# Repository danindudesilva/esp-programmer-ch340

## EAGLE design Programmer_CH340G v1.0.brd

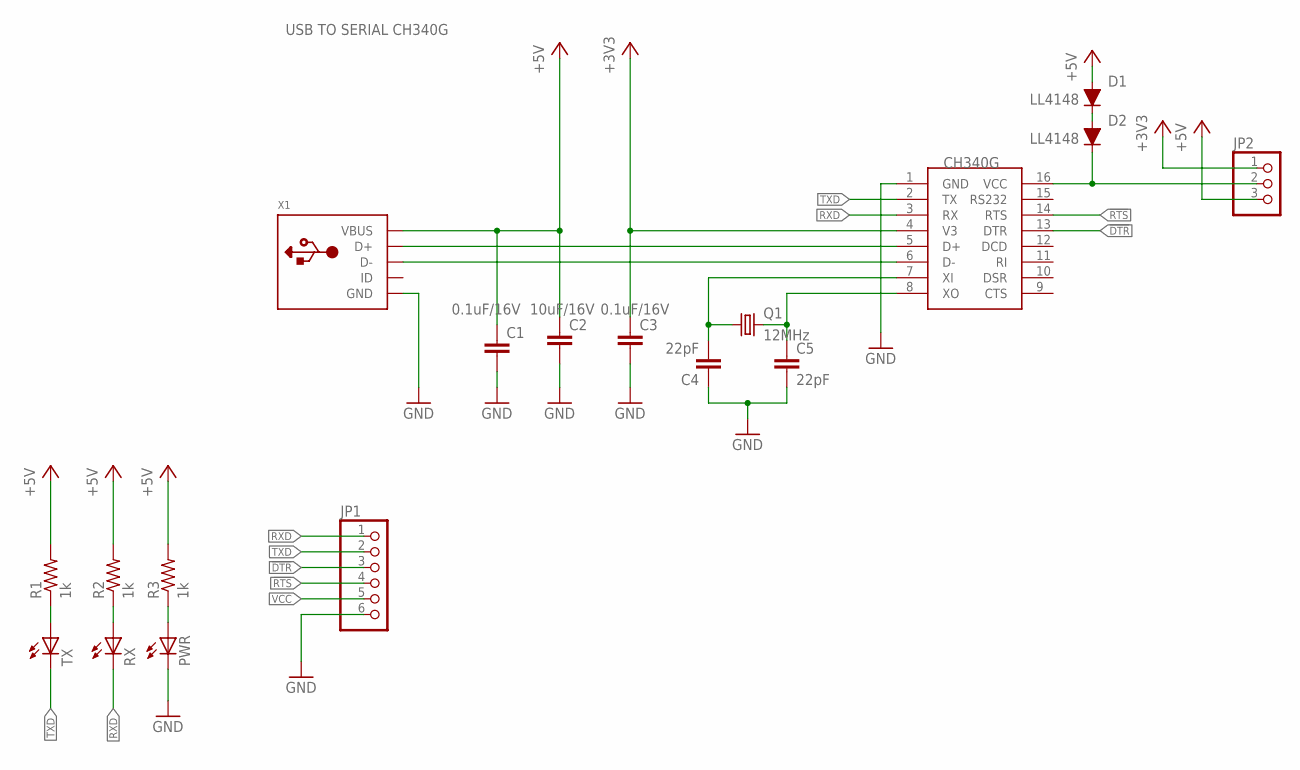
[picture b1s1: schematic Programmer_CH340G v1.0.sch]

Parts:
C1, C3: 0.1uF/16V; C0805K
C2: 10uF/16V; C0805K
C4, C5: 22pF; C0805K
D1, D2: LL4148; SOD80
JP1: PINHD-1X6; 1X06
JP2: PINHD-1X3; 1X03
PWR: LEDCHIP-LED0805; CHIP-LED0805
Q1: 12MHz; HC49U-V
R1, R2, R3: 1k; M0805
RX: LEDCHIP-LED0805; CHIP-LED0805
TX: LEDCHIP-LED0805; CHIP-LED0805
U1: CH340G; SOIC16
X1: USB_MICRO_20329_V2; 4UCONN_20329_V2

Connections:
!DTR: JP1.3, U1.13 (DTR)
!RTS: JP1.4, U1.14 (RTS)
+3V3: C3.1, JP2.1, U1.4 (V3)
+5V: C1.1, C2.1, D1.2 (A), JP2.3, R3.2, X1.VBUS
GND: C1.2, C2.2, C3.2, C4.1, C5.2, JP1.6, PWR.C, U1.1 (GND), X1.BASE@1 (GND), X1.BASE@2 (GND), X1.GND, X1.SPRT@1 (GND), X1.SPRT@2 (GND), X1.SPRT@3 (GND), X1.SPRT@4 (GND)
unnamed: PWR.A, R3.1
unnamed: C4.2, Q1.1, U1.7 (XI)
unnamed: D1.1 (C), D2.2 (A)
unnamed: C5.1, Q1.2, U1.8 (XO)
unnamed: U1.5 (D+), X1.D+
unnamed: U1.6 (D-), X1.D-
unnamed: R1.1, TX.A
unnamed: R2.1, RX.A
RXD: JP1.1, RX.C, U1.3 (RX)
TXD: JP1.2, TX.C, U1.2 (TX)
VCC: D2.1 (C), JP1.5, JP2.2, R1.2, R2.2, U1.16 (VCC)

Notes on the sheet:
USB TO SERIAL CH340G

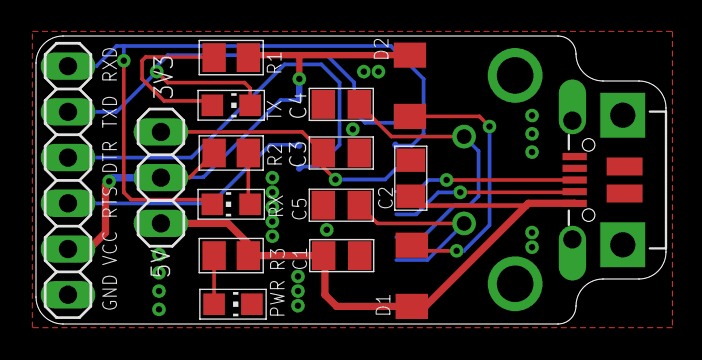
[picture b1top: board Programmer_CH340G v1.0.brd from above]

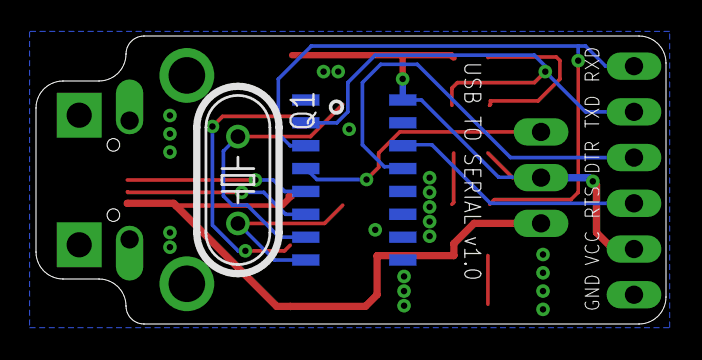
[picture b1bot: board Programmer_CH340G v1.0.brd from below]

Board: 2 copper layers, 35.0 x 16.0 mm, 18 parts (2 on the bottom side), 16 nets.

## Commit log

2020-07-16 Adds PDFs
